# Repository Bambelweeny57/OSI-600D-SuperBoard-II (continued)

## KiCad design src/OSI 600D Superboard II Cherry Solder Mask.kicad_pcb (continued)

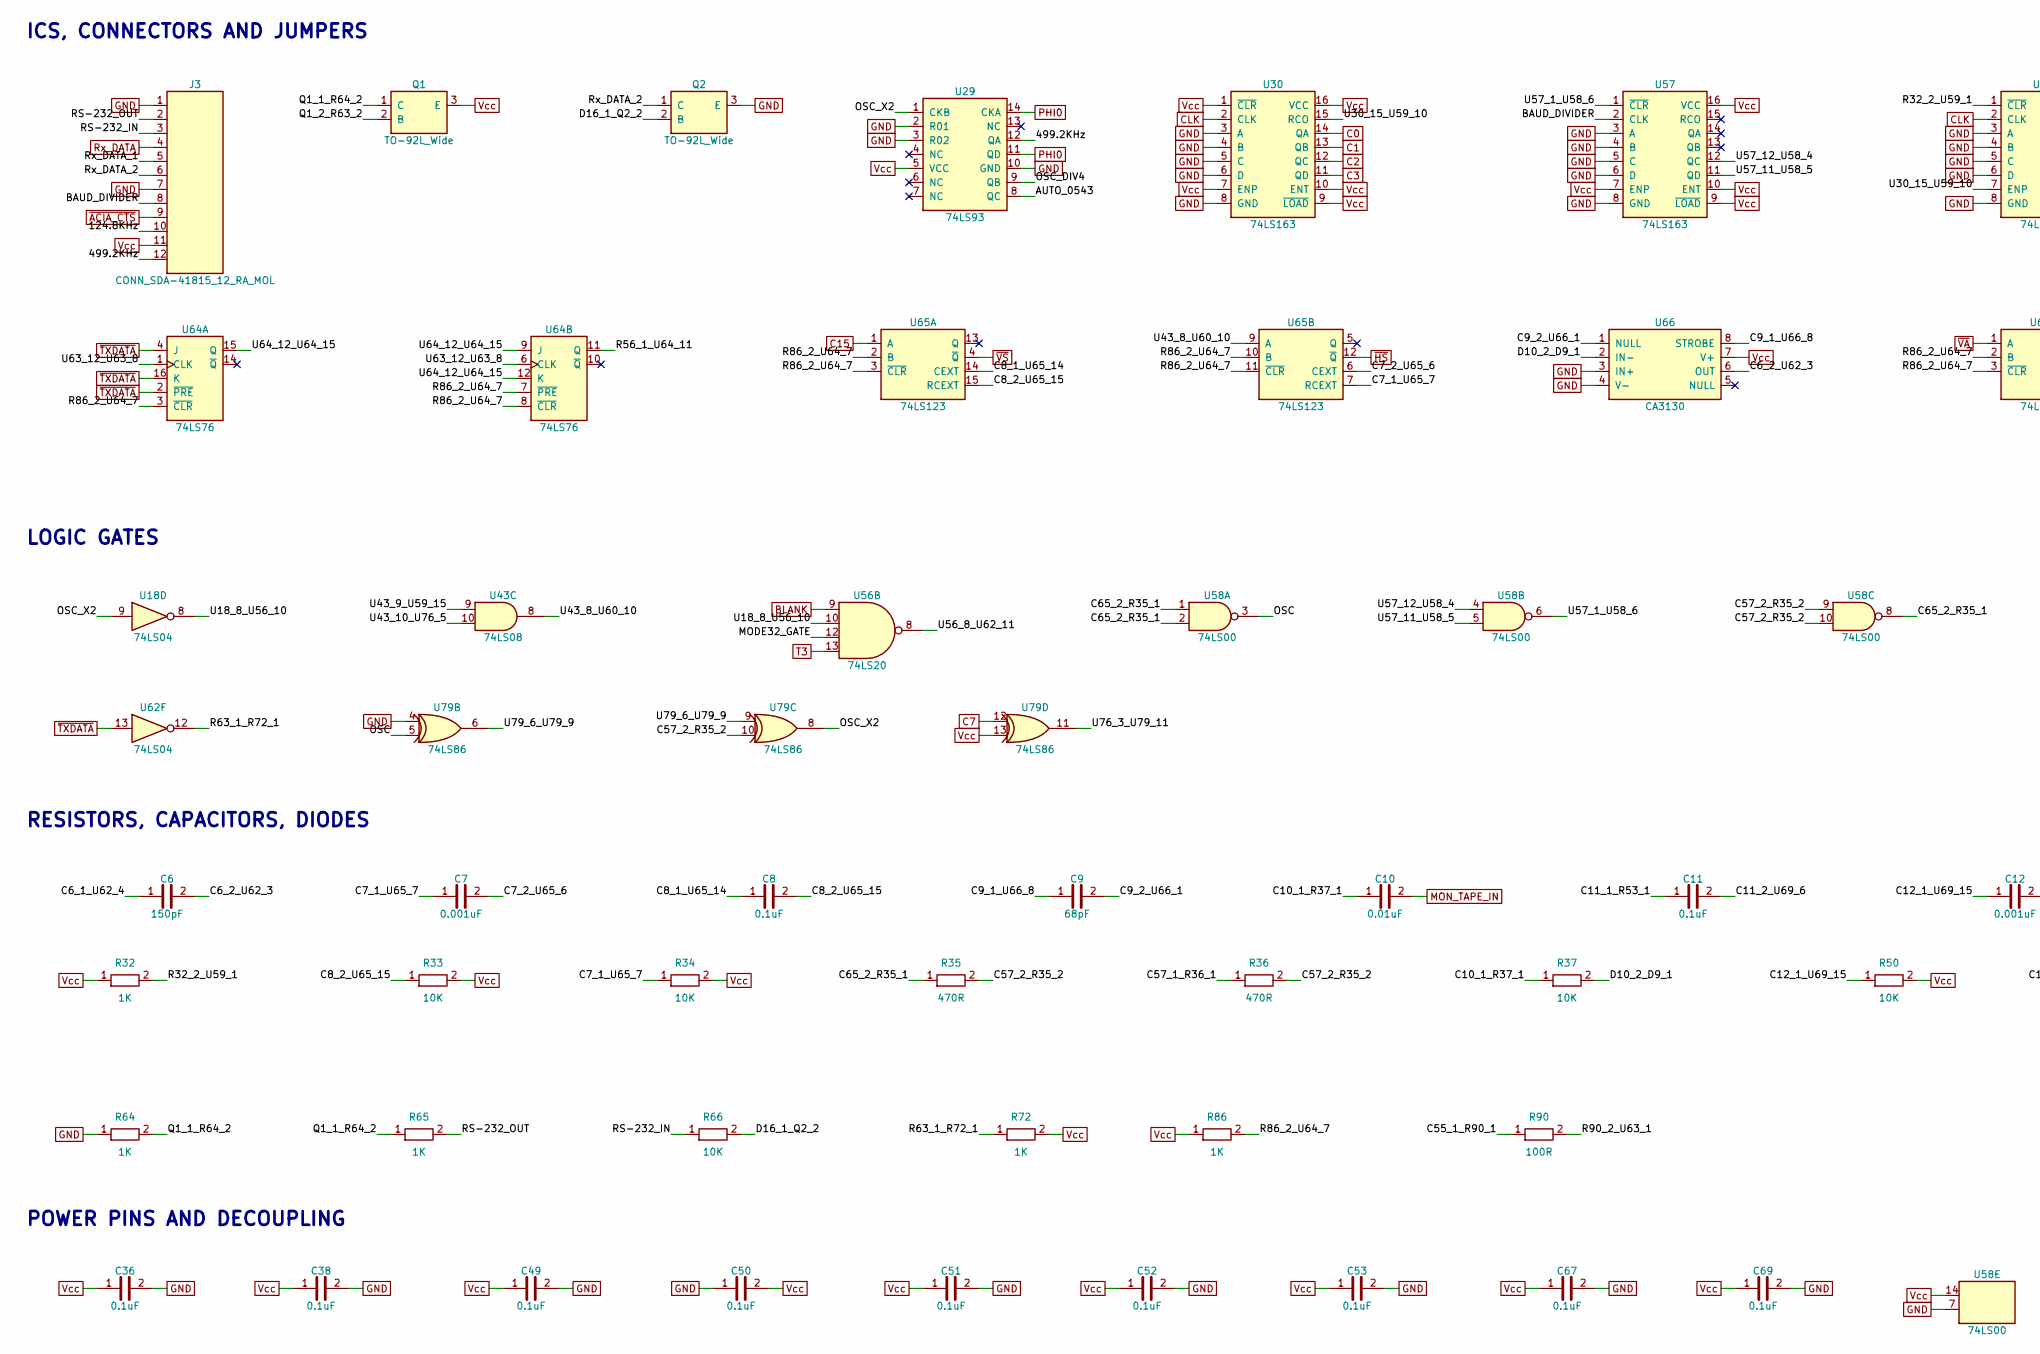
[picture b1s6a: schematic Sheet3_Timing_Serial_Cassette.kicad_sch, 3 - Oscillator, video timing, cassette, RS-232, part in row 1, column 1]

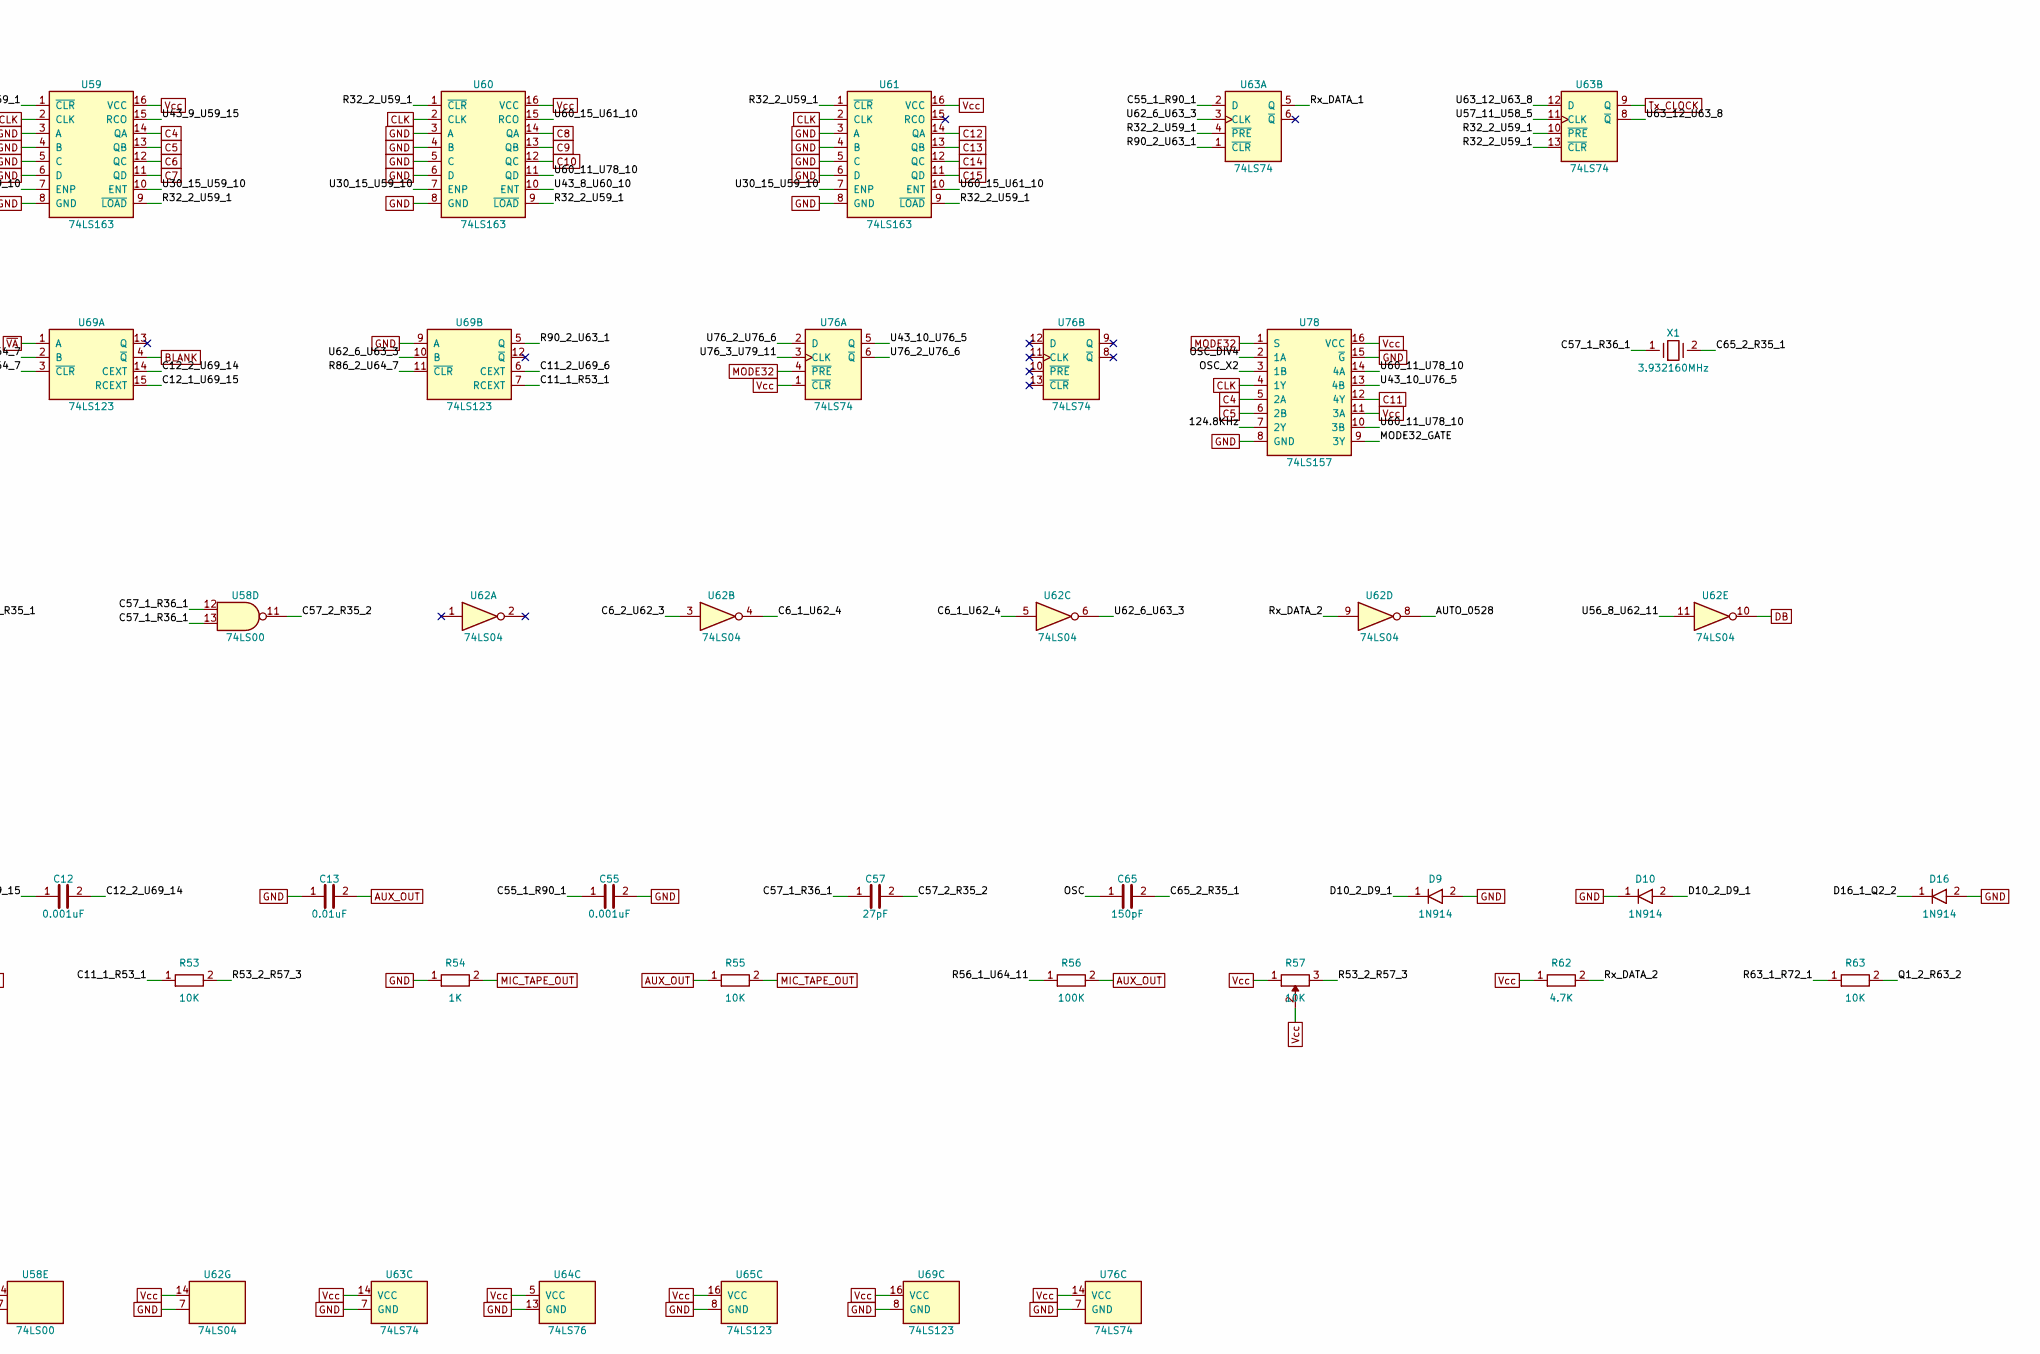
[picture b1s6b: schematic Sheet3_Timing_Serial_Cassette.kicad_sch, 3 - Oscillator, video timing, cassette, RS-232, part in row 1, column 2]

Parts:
C6, C65: 150pF; C_Rect_L10.0mm_W3.0mm_P7.50mm_FKS3_FKP3
C7, C12, C55: 0.001uF; C_Rect_L10.0mm_W3.0mm_P7.50mm_FKS3_FKP3
C8, C11, C36, C38, C49, C50, C51, C52, C53, C67, C69: 0.1uF; C_Rect_L10.0mm_W3.0mm_P7.50mm_FKS3_FKP3
C9: 68pF; C_Rect_L10.0mm_W3.0mm_P7.50mm_FKS3_FKP3
C10, C13: 0.01uF; C_Rect_L10.0mm_W3.0mm_P7.50mm_FKS3_FKP3
C57: 27pF; C_Disc_D10.0mm_W2.5mm_P5.00mm
D9, D10: 1N914; D_DO-34_SOD68_P10.16mm_Horizontal
D16: 1N914; D_T-1_P5.08mm_Horizontal
J3: CONN_SDA-41815_12_RA_MOL
Q1, Q2: TO-92L_Wide
R32, R54, R72, R86: 1K; R_Axial_DIN0207_L6.3mm_D2.5mm_P2.54mm_Vertical
R33, R34, R50, R53, R55, R63, R66: 10K; R_Axial_DIN0207_L6.3mm_D2.5mm_P2.54mm_Vertical
R35, R36: 470R; R_Axial_DIN0207_L6.3mm_D2.5mm_P2.54mm_Vertical
R37: 10K; R_Yageo_L3.6mm_D1.6mm_P12.70mm_Horizontal
R56: 100K; R_Axial_DIN0207_L6.3mm_D2.5mm_P2.54mm_Vertical
R57: 10K; Potentiometer_Bourns_3266Y_Vertical
R62: 4.7K; R_Axial_DIN0207_L6.3mm_D2.5mm_P2.54mm_Vertical
R64: 1K; R_Axial_DIN0516_L15.5mm_D5.0mm_P22.60mm_Horizontal
R65: 1K; R_Axial_DIN0309_L9.0mm_D3.2mm_P20.32mm_Horizontal
R90: 100R; R_Axial_DIN0207_L6.3mm_D2.5mm_P2.54mm_Vertical
U18, U62: 74LS04; DIP-14_W7.62mm_LongPads
U29: 74LS93; DIP-14_W7.62mm_LongPads
U30, U57, U59, U60, U61: 74LS163; DIP-16_W7.62mm_LongPads
U43: 74LS08; DIP-14_W7.62mm_LongPads
U56: 74LS20; DIP-14_W7.62mm_LongPads
U58: 74LS00; DIP-14_W7.62mm_LongPads
U63, U76: 74LS74; DIP-14_W7.62mm_LongPads
U64: 74LS76; DIP-16_W7.62mm_LongPads
U65, U69: 74LS123; DIP-16_W7.62mm_LongPads
U66: CA3130; DIP-8_W7.62mm_LongPads
U78: 74LS157; DIP-16_W7.62mm_LongPads
U79: 74LS86; DIP-14_W7.62mm_LongPads
X1: 3.932160MHz; Crystal_HC51_Horizontal

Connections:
124.8KHz: J3.10, U78.7 (2Y)
499.2KHz: J3.12, U29.12 (QA)
AUTO_0528: U62.8
AUTO_0543: U29.8 (QC)
AUX_OUT: C13.2, R55.1, R56.2; also elsewhere on the board
BAUD_DIVIDER: J3.8, U57.2 (CLK)
BLANK: U56.9, U69.4 (~Q); also elsewhere on the board
C0: U30.14 (QA); also elsewhere on the board
C1: U30.13 (QB); also elsewhere on the board
C2: U30.12 (QC); also elsewhere on the board
C3: U30.11 (QD); also elsewhere on the board
C4: U59.14 (QA), U78.5 (2A); also elsewhere on the board
C5: U59.13 (QB), U78.6 (2B); also elsewhere on the board
C6: U59.12 (QC); also elsewhere on the board
C6_1_U62_4: C6.1, U62.4, U62.5
C6_2_U62_3: C6.2, U62.3, U66.6 (OUT)
C7: U59.11 (QD), U79.12; also elsewhere on the board
C7_1_U65_7: C7.1, R34.1, U65.7 (RCEXT)
C7_2_U65_6: C7.2, U65.6 (CEXT)
C8: U60.14 (QA); also elsewhere on the board
C8_1_U65_14: C8.1, U65.14 (CEXT)
C8_2_U65_15: C8.2, R33.1, U65.15 (RCEXT)
C9: U60.13 (QB); also elsewhere on the board
C9_1_U66_8: C9.1, U66.8 (STROBE)
C9_2_U66_1: C9.2, U66.1 (NULL)
C10: U60.12 (QC); also elsewhere on the board
C10_1_R37_1: C10.1, R37.1
C11: U78.12 (4Y); also elsewhere on the board
C11_1_R53_1: C11.1, R53.1, U69.7 (RCEXT)
C11_2_U69_6: C11.2, U69.6 (CEXT)
C12: U61.14 (QA); also elsewhere on the board
C12_1_U69_15: C12.1, R50.1, U69.15 (RCEXT)
C12_2_U69_14: C12.2, U69.14 (CEXT)
C13: U61.13 (QB); also elsewhere on the board
C14: U61.12 (QC); also elsewhere on the board
C15: U61.11 (QD), U65.1 (A); also elsewhere on the board
C55_1_R90_1: C55.1, R90.1, U63.2 (D)
C57_1_R36_1: C57.1, R36.1, U58.12, U58.13, X1.1
C57_2_R35_2: C57.2, R35.2, R36.2, U58.9, U58.10, U58.11, U79.10
C65_2_R35_1: C65.2, R35.1, U58.1, U58.2, U58.8, X1.2
CLK: U30.2 (CLK), U59.2 (CLK), U60.2 (CLK), U61.2 (CLK), U78.4 (1Y); also elsewhere on the board
D10_2_D9_1: D9.1, D10.2, R37.2, U66.2 (IN-)
D16_1_Q2_2: D16.1, Q2.2 (B), R66.2
DB: U62.10; also elsewhere on the board
GND: C13.1, C36.2, C38.2, C49.2, C50.1, C51.2, C52.2, C53.2, C55.2, C67.2, C69.2, D9.2, D10.1, D16.2, J3.1, J3.7, Q2.3 (E), R54.1, R64.1, U29.2 (R01), U29.3 (R02), U29.10 (GND), U30.3 (A), U30.4 (B), U30.5 (C), U30.6 (D), U30.8 (GND), U57.3 (A), U57.4 (B), U57.5 (C), U57.6 (D), U57.8 (GND), U58.7 (GND), U59.3 (A), U59.4 (B), U59.5 (C), U59.6 (D), U59.8 (GND), U60.3 (A), U60.4 (B), U60.5 (C), U60.6 (D), U60.8 (GND), U61.3 (A), U61.4 (B), U61.5 (C), U61.6 (D), U61.8 (GND), U62.7 (GND), U63.7 (GND), U64.13 (GND), U65.8 (GND), U66.3 (IN+), U66.4 (V-), U69.8 (GND), U69.9 (A), U76.7 (GND), U78.8 (GND), U78.15 (~G), U79.4; also elsewhere on the board
MIC_TAPE_OUT: R54.2, R55.2; also elsewhere on the board
MODE32: U76.4 (~PRE), U78.1 (S); also elsewhere on the board
MODE32_GATE: U56.12, U78.9 (3Y)
MON_TAPE_IN: C10.2; also elsewhere on the board
OSC: C65.1, U58.3, U79.5
OSC_DIV4: U29.9 (QB), U78.2 (1A)
OSC_X2: U18.9, U29.1 (CKB), U78.3 (1B), U79.8
PHI0: U29.11 (QD), U29.14 (CKA); also elsewhere on the board
Q1_1_R64_2: Q1.1 (C), R64.2, R65.1
Q1_2_R63_2: Q1.2 (B), R63.2
R32_2_U59_1: R32.2, U59.1 (~CLR), U59.9 (~LOAD), U60.1 (~CLR), U60.9 (~LOAD), U61.1 (~CLR), U61.9 (~LOAD), U63.4 (~PRE), U63.10 (~PRE), U63.13 (~CLR)
R53_2_R57_3: R53.2, R57.3
R56_1_U64_11: R56.1, U64.11 (Q)
R63_1_R72_1: R63.1, R72.1, U62.12
R86_2_U64_7: R86.2, U64.3 (~CLR), U64.7 (~PRE), U64.8 (~CLR), U65.2 (B), U65.3 (~CLR), U65.10 (B), U65.11 (~CLR), U69.2 (B), U69.3 (~CLR), U69.11 (~CLR)
R90_2_U63_1: R90.2, U63.1 (~CLR), U69.5 (Q)
RS-232_IN: J3.3, R66.1
RS-232_OUT: J3.2, R65.2
Rx_DATA: J3.4; also elsewhere on the board
Rx_DATA_1: J3.5, U63.5 (Q)
Rx_DATA_2: J3.6, Q2.1 (C), R62.2, U62.9
T3: U56.13; also elsewhere on the board
Tx_CLOCK: U63.9 (Q); also elsewhere on the board
U18_8_U56_10: U18.8, U56.10
U30_15_U59_10: U30.15 (RCO), U59.7 (ENP), U59.10 (ENT), U60.7 (ENP), U61.7 (ENP)
U43_8_U60_10: U43.8, U60.10 (ENT), U65.9 (A)
U43_9_U59_15: U43.9, U59.15 (RCO)
U43_10_U76_5: U43.10, U76.5 (Q), U78.13 (4B)
U56_8_U62_11: U56.8, U62.11
U57_1_U58_6: U57.1 (~CLR), U58.6
U57_11_U58_5: U57.11 (QD), U58.5, U63.11 (CLK)
U57_12_U58_4: U57.12 (QC), U58.4
U60_11_U78_10: U60.11 (QD), U78.10 (3B), U78.14 (4A)
U60_15_U61_10: U60.15 (RCO), U61.10 (ENT)
U62_6_U63_3: U62.6, U63.3 (CLK), U69.10 (B)
U63_12_U63_8: U63.8 (~Q), U63.12 (D), U64.1 (CLK), U64.6 (CLK)
U64_12_U64_15: U64.9 (J), U64.12 (K), U64.15 (Q)
U76_2_U76_6: U76.2 (D), U76.6 (~Q)
U76_3_U79_11: U76.3 (CLK), U79.11
U79_6_U79_9: U79.6, U79.9
Vcc: C36.1, C38.1, C49.1, C50.2, C51.1, C52.1, C53.1, C67.1, C69.1, J3.11, Q1.3 (E), R32.1, R33.2, R34.2, R50.2, R57.1, R57.2, R62.1, R72.2, R86.1, U29.5 (VCC), U30.1 (~CLR), U30.7 (ENP), U30.9 (~LOAD), U30.10 (ENT), U30.16 (VCC), U57.7 (ENP), U57.9 (~LOAD), U57.10 (ENT), U57.16 (VCC), U58.14 (VCC), U59.16 (VCC), U60.16 (VCC), U61.16 (VCC), U62.14 (VCC), U63.14 (VCC), U64.5 (VCC), U65.16 (VCC), U66.7 (V+), U69.16 (VCC), U76.1 (~CLR), U76.14 (VCC), U78.11 (3A), U78.16 (VCC), U79.13; also elsewhere on the board
~ACIA_CTS: J3.9; also elsewhere on the board
~HS: U65.12 (~Q); also elsewhere on the board
~TXDATA: U62.13, U64.2 (~PRE), U64.4 (J), U64.16 (K); also elsewhere on the board
~VA: U69.1 (A); also elsewhere on the board
~VS: U65.4 (~Q); also elsewhere on the board

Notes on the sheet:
ICS, CONNECTORS AND JUMPERS
LOGIC GATES
RESISTORS, CAPACITORS, DIODES
POWER PINS AND DECOUPLING

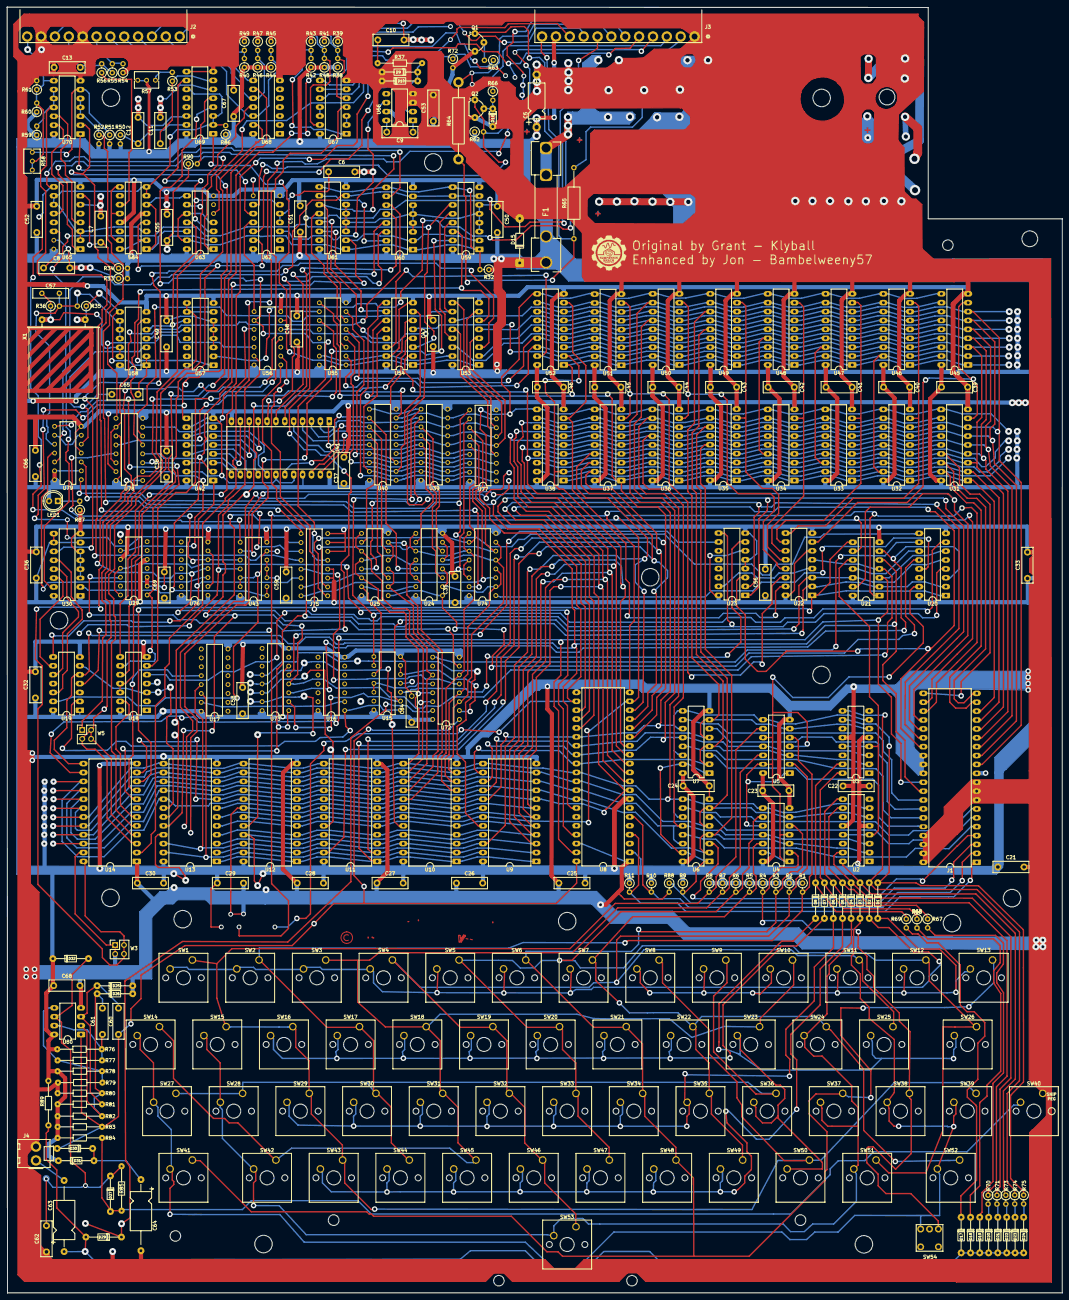
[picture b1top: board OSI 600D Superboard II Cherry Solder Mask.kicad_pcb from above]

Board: 2 copper layers, 301.5 x 367.3 mm, 313 parts (0 on the bottom side), 261 nets.

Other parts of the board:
H1, H5: MountingHole_4.5mm
H2, H3, H4, H7, H8, H9, H10, H11, H12, H13, H14, H18, H19: MountingHole_5.0mm
H6, H17, H20, H21: MountingHole_3.0mm
H15, H16: MountingHole_3.05mm

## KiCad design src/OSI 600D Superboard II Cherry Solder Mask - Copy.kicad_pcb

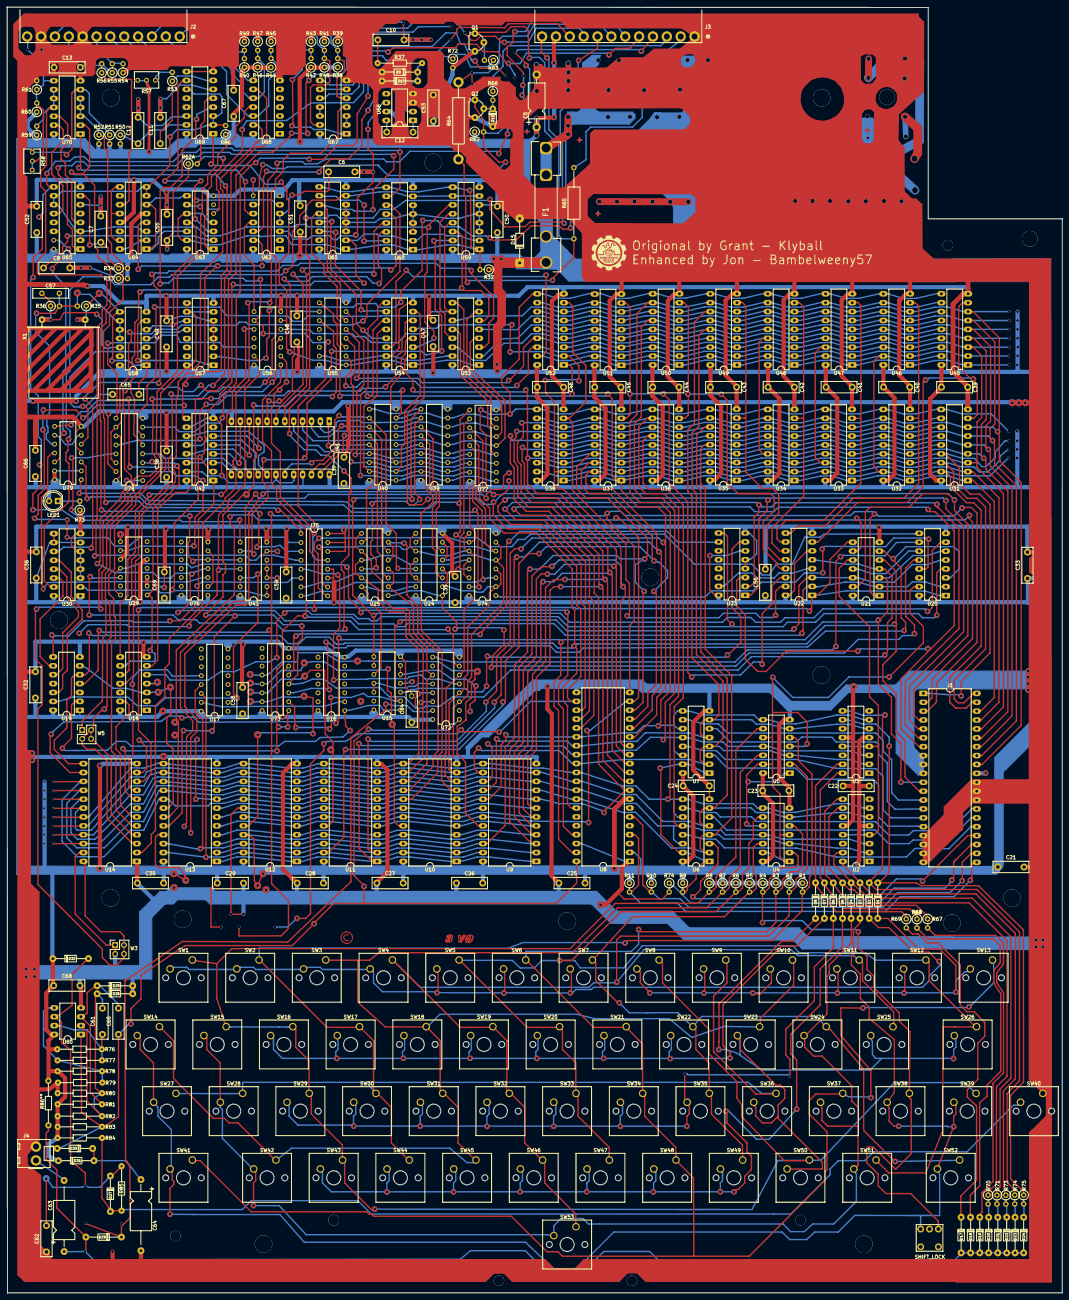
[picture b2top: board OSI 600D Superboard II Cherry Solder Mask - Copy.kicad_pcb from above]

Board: 2 copper layers, 301.5 x 367.3 mm, 292 parts (0 on the bottom side), 2 nets.

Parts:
C5: 33uf; CP_Axial_L10.0mm_D4.5mm_P15.00mm_Horizontal
C6, C7, C8, C10, C11, C12, C13, C21, C22, C23, C24, C25, C26, C27, C28, C29, C30, C32, C33, C35, C36, C37, C38, C39, C40, C41, C42, C43, C44, C45, C46, C47, C48, C49, C50, C51, C52, C53, C54, C55, C56, C58, C59, C60, C61, C62, C65, C66, C67, C68, C69: C_Rect_L10.0mm_W3.0mm_P7.50mm_FKS3_FKP3
C12#2: 1000pf; C_Rect_L10.0mm_W3.0mm_P7.50mm_FKS3_FKP3
C57: 27pf; C_Disc_D10.0mm_W2.5mm_P5.00mm
C63, C64: ?; CP_Axial_L11.0mm_D6.0mm_P20.32mm_Horizontal
D1, D2, D3, D4, D5, D6, D7, D8, D9, D10, D17, D18, D19, D20, D21, D22, D23, D24, D25, D26, D27, D29, D30, D31, D32: 1N914; D_DO-34_SOD68_P10.16mm_Horizontal
D15: 1N4001; D_DO-35_SOD27_P12.70mm_Horizontal
D16: 1N914; D_T-1_P5.08mm_Horizontal
F1: 5A; Fuseholder_Clip-6.3x32mm_Littelfuse_102_Inline_P34.21x7.62m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
J1: DIP40; DIP-40_W15.24mm_LongPads
J2, J3: CONN_SDA-41815_12_RA_MOL
J4: Molex_KK-396_A-41791-0002_1x02_P3.96mm_Vertical
J75: DIP16; DIP-16_W7.62mm_LongPads
LED1: LED_D5.0mm
Q1, Q2: TO-92L_Wide
R1, R2, R3, R4, R5, R6, R7, R8, R10, R11: 4.7K; R_Axial_DIN0207_L6.3mm_D2.5mm_P2.54mm_Vertical
R9: 220R; R_Axial_DIN0207_L6.3mm_D2.5mm_P2.54mm_Vertical
R32, R75: 1K; R_Axial_DIN0207_L6.3mm_D2.5mm_P2.54mm_Vertical
R33, R50: 10K; R_Axial_DIN0207_L6.3mm_D2.5mm_P2.54mm_Vertical
R34, R38, R39, R40, R41, R42, R43, R44, R45, R46, R47, R48, R49, R51, R52, R53, R54, R55, R56, R59, R60, R61, R62, R62A, R63, R66, R72, R86: R_Axial_DIN0207_L6.3mm_D2.5mm_P2.54mm_Vertical
R35, R36, R73: 470R; R_Axial_DIN0207_L6.3mm_D2.5mm_P2.54mm_Vertical
R37, R76, R77, R78, R79, R80, R81, R82, R83, R84, R85: R_Yageo_L3.6mm_D1.6mm_P12.70mm_Horizontal
R57: 10K; Potentiometer_Bourns_3266Y_Vertical
R58: 5K; Potentiometer_Bourns_3266Y_Vertical
R64: 1K; R_Axial_DIN0516_L15.5mm_D5.0mm_P22.60mm_Horizontal
R65: R_Axial_DIN0309_L9.0mm_D3.2mm_P20.32mm_Horizontal
R67: 8.2K; R_Axial_DIN0207_L6.3mm_D2.5mm_P2.54mm_Vertical
R68: 3.9K; R_Axial_DIN0207_L6.3mm_D2.5mm_P2.54mm_Vertical
R69: 2K; R_Axial_DIN0207_L6.3mm_D2.5mm_P2.54mm_Vertical
R70: 16K; R_Axial_DIN0207_L6.3mm_D2.5mm_P2.54mm_Vertical
R71: 33K; R_Axial_DIN0207_L6.3mm_D2.5mm_P2.54mm_Vertical
R73#2: 68K; R_Axial_DIN0207_L6.3mm_D2.5mm_P2.54mm_Vertical
R74: 390R; R_Axial_DIN0207_L6.3mm_D2.5mm_P2.54mm_Vertical
R74#2: 510R; R_Axial_DIN0207_L6.3mm_D2.5mm_P2.54mm_Vertical
R86**: 510R; R_Yageo_L3.6mm_D1.6mm_P12.70mm_Horizontal
SHIFT_LOCK: Shift_Lock_Switch
SW1, SW2, SW3, SW4, SW5, SW6, SW7, SW8, SW9, SW10, SW11, SW12, SW13, SW14, SW15, SW16, SW17, SW18, SW19, SW20, SW21, SW22, SW23, SW24, SW25, SW27, SW28, SW29, SW30, SW31, SW32, SW33, SW34, SW35, SW36, SW37, SW38, SW39, SW40, SW42, SW43, SW44, SW45, SW46, SW47, SW48, SW49, SW50, SW51, SW53: SW_Cherry_MX_1.00u_PCB
SW26, SW41, SW52: SW_Cherry_MX_1.50u_PCB
U2, U3: 74LS75; DIP-16_W7.62mm_LongPads
U4, U5: 74LS125; DIP-14_W7.62mm_LongPads
U6, U7, U24, U25, U74: 8T28; DIP-16_W7.62mm_LongPads
U8: 6502; DIP-40_W15.24mm_LongPads
U9, U10, U11, U12, U13: 27C16 / 2816; DIP-24_W15.24mm_LongPads
U14: 6850; DIP-24_W15.24mm_LongPads
U15: 74LS02; DIP-14_W7.62mm_LongPads
U16, U18, U21, U62: 74LS04; DIP-14_W7.62mm_LongPads
U17: 74LS159; DIP-16_W7.62mm_LongPads
U19, U56: 74LS20; DIP-14_W7.62mm_LongPads
U20, U22, U23, U73: 74LS138; DIP-16_W7.62mm_LongPads
U29: 74LS93; DIP-14_W7.62mm_LongPads
U30, U57, U59, U60, U61: 74LS163; DIP-16_W7.62mm_LongPads
U31, U32, U33, U34, U35, U36, U37, U38, U39, U40, U45, U46, U47, U48, U49, U50, U51, U52, U77: 2114; DIP-18_W7.62mm_LongPads
U41: CHAR_GEN; DIP-24_W15.24mm_LongPads
U42: 74LS165; DIP-16_W7.62mm_LongPads
U43: 74LS08; DIP-14_W7.62mm_LongPads
U53, U55, U78: 74LS157; DIP-16_W7.62mm_LongPads
U54: 74LS175; DIP-16_W7.62mm_LongPads
U58: 74LS00; DIP-14_W7.62mm_LongPads
U63, U76: 74LS74; DIP-14_W7.62mm_LongPads
U64: 74LS76; DIP-16_W7.62mm_LongPads
U65, U69: 74LS123; DIP-16_W7.62mm_LongPads
U66: CA3130; DIP-8_W7.62mm_LongPads
U67: 74LS14; DIP-14_W7.62mm_LongPads
U68: 74LS17; DIP-14_W7.62mm_LongPads
U70: 74LS03; DIP-14_W7.62mm_LongPads
U72: 74LS174; DIP-16_W7.62mm_LongPads
U79: 74LS86; DIP-14_W7.62mm_LongPads
U80: LM393; DIP-8_W7.62mm_LongPads
W3, W5: PinHeader_2x02_P2.54mm_Vertical
X1: Crystal_HC51_Horizontal

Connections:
GND: U36.9, U37.9
Vcc: U36.18, U37.18
